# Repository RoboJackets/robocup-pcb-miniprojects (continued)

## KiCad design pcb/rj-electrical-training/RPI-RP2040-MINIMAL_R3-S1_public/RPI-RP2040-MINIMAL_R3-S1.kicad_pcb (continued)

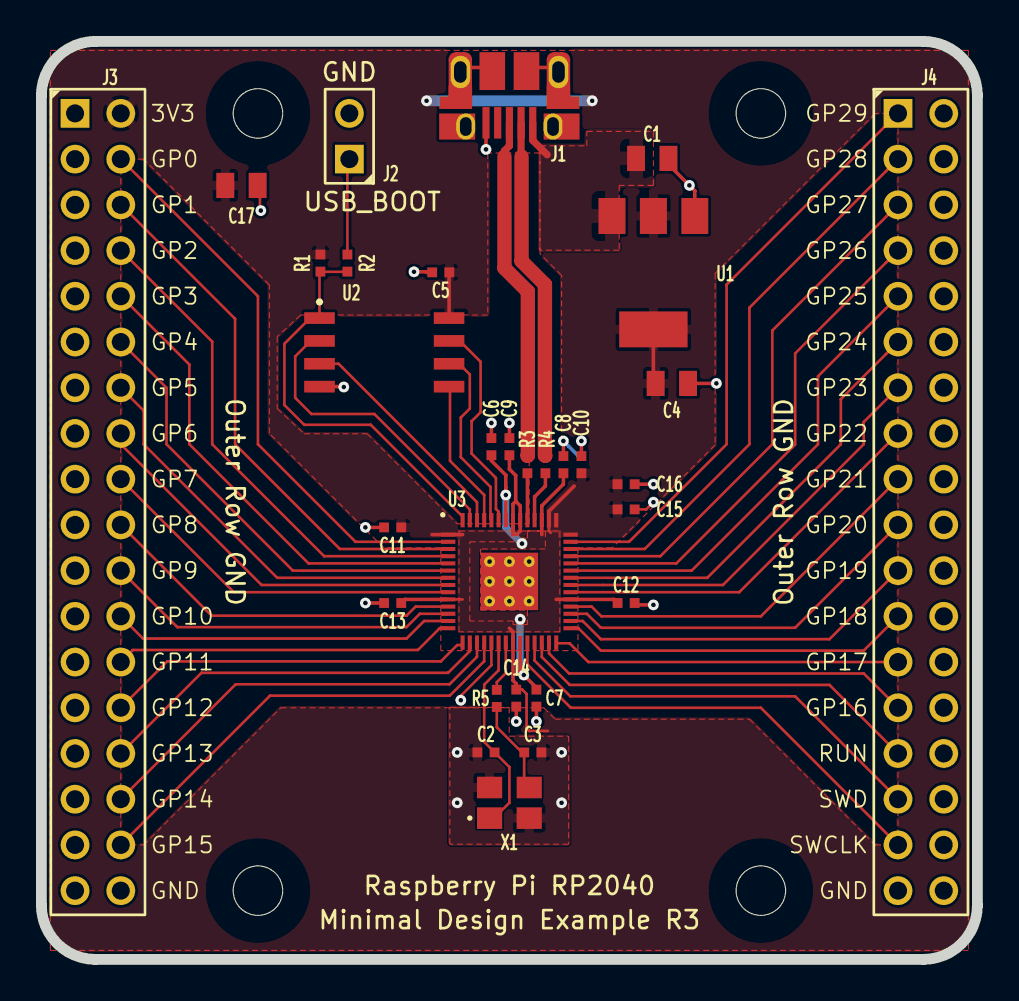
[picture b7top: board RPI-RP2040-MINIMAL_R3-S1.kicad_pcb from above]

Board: 2 copper layers, 52.0 x 51.0 mm, 34 parts (0 on the bottom side), 51 nets.

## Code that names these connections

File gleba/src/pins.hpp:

#pragma once
// GPIO assignments, schematic Rev 11.7.1
// Owner: shared (agree before changing)

// ---- I2C: one bus per device (only 2 controllers -> switch with gpio_set_function) ----
#define PIN_SDA_IMU      0   // I2C0
#define PIN_SCL_IMU      1   // I2C0
#define PIN_SDA_TEMP     2   // I2C1
#define PIN_SCL_TEMP     3   // I2C1
#define PIN_SDA_HALL     4   // I2C0
#define PIN_SCL_HALL     5   // I2C0
#define PIN_SDA_GPIO     22  // I2C1 (GPIO expander)
#define PIN_SCL_GPIO     23  // I2C1
#define PIN_SDA_COLOR    24  // I2C0
#define PIN_SCL_COLOR    25  // I2C0
#define PIN_SDA_LED      26  // I2C1 (LED driver)
#define PIN_SCL_LED      27  // I2C1

#define I2C_BAUD_HZ      (400 * 1000)

#define PIN_LED_SDB      6   // IS31FL3254 enable, high = on (100k pull-down)

// ---- Debug LEDs (active-low: write 0 to turn on) ----
#define PIN_LED_D39      8
#define PIN_LED_D40      9
#define PIN_LED_D41      10

// ---- Buttons (active-low: read 0 when pressed, RC debounced) ----
#define PIN_BUTTON_1     16  // S4
#define PIN_BUTTON_2     17  // S5

// ---- SPI OUT: SPI1, we are MASTER (to next board, J7) ----
#define PIN_SPI_OUT_MISO 12  // SPI1 RX  (we receive)
#define PIN_SPI_OUT_CSN  13  // SPI1 CSn
#define PIN_SPI_OUT_SCK  14  // SPI1 SCK
#define PIN_SPI_OUT_MOSI 15  // SPI1 TX  (we send)

// ---- SPI IN: SPI0, we are SLAVE (from previous board, J9) ----
#define PIN_SPI_IN_SCK   18  // SPI0 SCK
#define PIN_SPI_IN_MISO  19  // SPI0 TX  (we send back to master)
#define PIN_SPI_IN_MOSI  20  // SPI0 RX  (we receive)
#define PIN_SPI_IN_CSN   21  // SPI0 CSn

#define SPI_BAUD_HZ      (1000 * 1000)   // 1 MHz, mode 3 (CPOL = 1, CPHA = 1)

// Unused: GPIO 7, 11, 28, 29

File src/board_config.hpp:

/**
 * @file board_config.hpp
 * @brief Single source of truth for every hardware assignment the firmware uses.
 *
 * Two targets share this file:
 *   - Fulgora PCB            (FULGORA_BOARD defined by boards/fulgora.h)
 *   - Raspberry Pi Pico dev  (default build)
 *
 * The Pico differs only where its own hardware occupies a pin
 * (GPIO23 = SMPS mode, GPIO24 = VBUS sense, GPIO25 = on-board LED,
 * GPIO29 = VSYS sense). Everything else is identical, so code tested
 * on the Pico runs unchanged on the PCB.
 *
 * Source of the PCB values: fulgora-branch schematic + Onboarding Pinouts sheet.
 * Every pin choice below is checked at compile time against the RP2040
 * GPIO function table (see the static_asserts at the bottom).
 */
#pragma once

#include <cstdint>

#include "hardware/i2c.h"
#include "hardware/spi.h"

namespace board {

//inter-board SPI

struct SpiPins {
    uint8_t instance;  //0 = spi0, 1 = spi1
    uint8_t rx; //receive pin
    uint8_t csn; //chip select, active low
    uint8_t sck; //serial clock
    uint8_t tx; //transmit pin
};

// IN connector, we're the slave, Receives packets from the previous board.
inline constexpr SpiPins kSpiIn{0, /*rx*/ 0, /*csn*/ 1, /*sck*/ 2, /*tx*/ 3};

// OUT connector, we're the master, Sends packets to the next board.
inline constexpr SpiPins kSpiOut{1, /*rx*/ 12, /*csn*/ 13, /*sck*/ 14, /*tx*/ 15};

// from the firmware README: 1 MHz, mode 3
inline constexpr uint32_t kSpiBaudHz = 1'000'000;//clock frequency
inline constexpr spi_cpol_t kSpiCpol = SPI_CPOL_1;//Clock is high when idle
inline constexpr spi_cpha_t kSpiCpha = SPI_CPHA_1;//Sample on the second clock edge
inline constexpr uint8_t kSpiDataBits = 8;//8 bits per transfer unit

//I2C devices

// same order as the sections in the packet
enum class Device : uint8_t {
    Imu = 0,
    Temperature,
    HallEffect,
    GpioExpander,
    ColorSensor,
    LedController,
    Count
};

inline constexpr uint8_t kDeviceCount = static_cast<uint8_t>(Device::Count);

struct I2cDevicePins {
    const char *name; //Human-readable device name
    uint8_t instance;  // 0 = i2c0, 1 = i2c1 (depends on which GPIOs, not a choice)
    uint8_t sda;//data pin
    uint8_t scl;//clock pin
    uint8_t address;   //7-bit I2C device address
};

inline constexpr uint32_t kI2cBaudHz = 400'000;  // all 6 parts support 400k

#ifdef FULGORA_BOARD
inline constexpr I2cDevicePins kI2cDevices[kDeviceCount] = {
    //  name               ctrl SDA SCL addr
    {"IMU ICM-42605",       0, 16, 17, 0x68},  // AD0 tied low
    {"Temp LM75ADP",        1, 18, 19, 0x48},  // A2..A0 tied low
    {"Hall TMAG5273A2",     0, 20, 21, 0x35},  // default addr for the A variants
    {"GPIO TCA9534",        0,  4,  5, 0x20},  // A2..A0 tied low
    {"Color VEML3328",      1, 22, 23, 0x10},  // fixed
    {"LED IS31FL3254",      0, 24, 25, 0x30},  // AD tied low
};
#else
// Pico version, only the pins the Pico uses internally are moved
inline constexpr I2cDevicePins kI2cDevices[kDeviceCount] = {
    {"IMU ICM-42605",       0, 16, 17, 0x68},
    {"Temp LM75ADP",        1, 18, 19, 0x48},
    {"Hall TMAG5273A2",     0, 20, 21, 0x35},
    {"GPIO TCA9534",        0,  4,  5, 0x20},
    {"Color VEML3328",      1, 26, 27, 0x10},  // 22/23 on the PCB
    {"LED IS31FL3254",      0,  8,  9, 0x30},  // 24/25 on the PCB
};
#endif

inline constexpr const I2cDevicePins &device(Device d) {
    return kI2cDevices[static_cast<uint8_t>(d)];
}

// ---- buttons / LEDs ----

inline constexpr uint8_t kButtonCount = 2;
inline constexpr uint8_t kButtonPins[kButtonCount] = {6, 7};  // active low, 10k pull-ups on board

inline constexpr uint8_t kUserLedCount = 3;
#ifdef FULGORA_BOARD
inline constexpr uint8_t kUserLedPins[kUserLedCount] = {8, 9, 10};  // active high
inline constexpr uint8_t kLedDriverShutdownPin = 29;               // has a pull-down, drive high to enable
#else
inline constexpr uint8_t kUserLedPins[kUserLedCount] = {10, 11, 22};  // 8/9/10 on the PCB
inline constexpr uint8_t kLedDriverShutdownPin = 28;                 // 29 on the PCB
#endif

inline spi_inst_t *spiInstance(const SpiPins &p) { return p.instance ? spi1 : spi0; }
inline i2c_inst_t *i2cInstance(const I2cDevicePins &p) { return p.instance ? i2c1 : i2c0; }

// ---- compile-time pin checks (RP2040 datasheet 2.19.2) ----
namespace detail {

constexpr bool validGpio(uint8_t pin) { return pin <= 29; }

// SPI0/SPI1 swap every 8 pins, and inside each group of 4 it's RX, CSn, SCK, TX
constexpr uint8_t spiInstanceOf(uint8_t pin) { return (pin / 8) % 2; }
constexpr bool spiPinsValid(const SpiPins &p) {
    return validGpio(p.rx) && validGpio(p.tx) && validGpio(p.sck) && validGpio(p.csn) &&
           spiInstanceOf(p.rx) == p.instance && p.rx % 4 == 0 &&
           spiInstanceOf(p.csn) == p.instance && p.csn % 4 == 1 &&
           spiInstanceOf(p.sck) == p.instance && p.sck % 4 == 2 &&
           spiInstanceOf(p.tx) == p.instance && p.tx % 4 == 3;
}

// I2C0/I2C1 swap every 2 pins, even = SDA, odd = SCL
constexpr uint8_t i2cInstanceOf(uint8_t pin) { return (pin / 2) % 2; }
constexpr bool i2cPinsValid(const I2cDevicePins &p) {
    return validGpio(p.sda) && validGpio(p.scl) &&
           p.sda % 2 == 0 && p.scl == p.sda + 1 &&
           i2cInstanceOf(p.sda) == p.instance && p.address < 0x80;
}

constexpr bool allI2cValid() {
    for (const auto &d : kI2cDevices) {
        if (!i2cPinsValid(d)) return false;
    }
    return true;
}

}  // namespace detail

// build fails here if a pin above is wrong
static_assert(detail::spiPinsValid(kSpiIn), "kSpiIn pins do not match an RP2040 SPI block");
static_assert(detail::spiPinsValid(kSpiOut), "kSpiOut pins do not match an RP2040 SPI block");
static_assert(kSpiIn.instance != kSpiOut.instance, "IN and OUT must use different SPI controllers");
static_assert(detail::allI2cValid(), "an I2C device uses pins that are not SDA/SCL of its controller");

}  // namespace board
